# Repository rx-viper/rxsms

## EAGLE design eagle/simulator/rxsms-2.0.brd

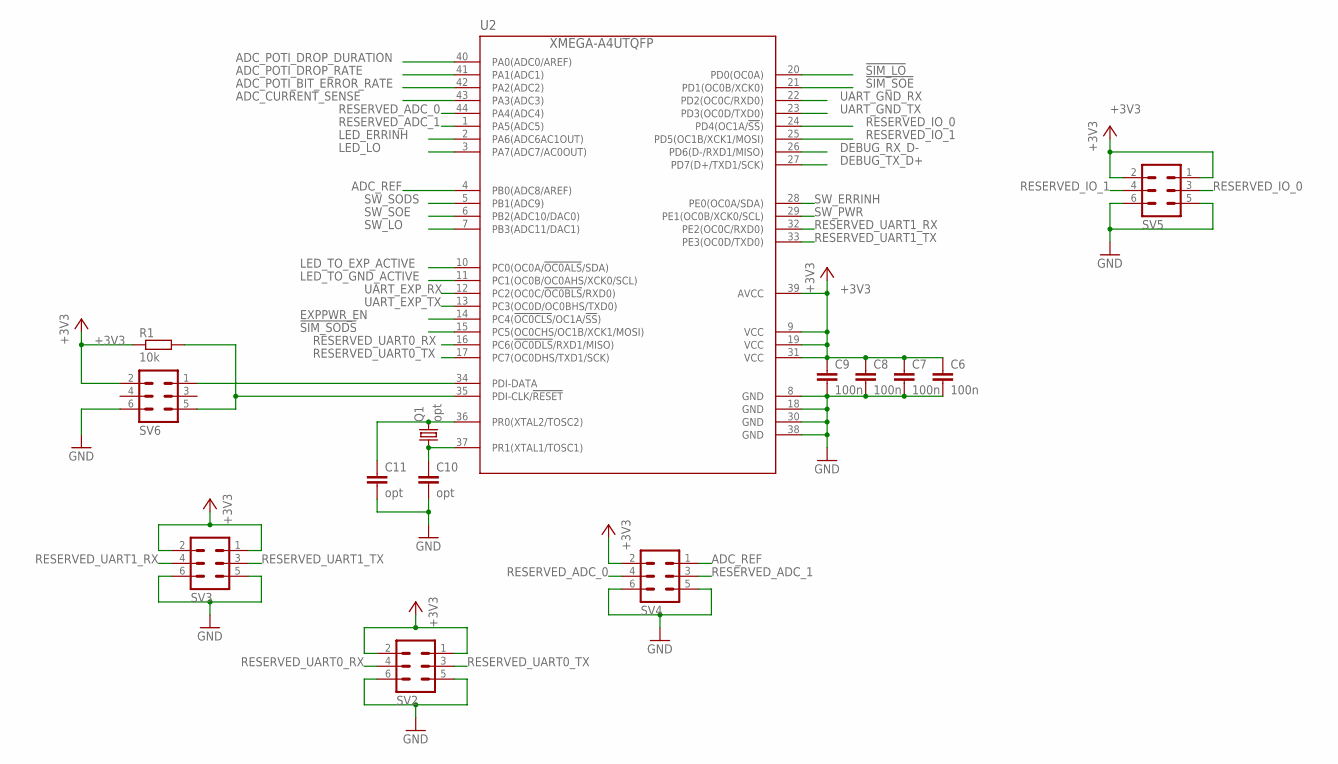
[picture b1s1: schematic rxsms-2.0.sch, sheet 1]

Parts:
C6, C7, C8, C9: 100n; C0805K
C10, C11: opt; C0805K
Q1: opt; HC49/S
R1: 10k; R0805
SV2, SV3, SV4, SV5, SV6: ML6
U2: XMEGA-A4UTQFP; TQFP44

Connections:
!SIM_LO: U2.20 (PD0(OC0A)); also elsewhere on the board
!SIM_SODS: U2.15 (PC5(OC0CHS/OC1B/XCK1/MOSI)); also elsewhere on the board
!SIM_SOE: U2.21 (PD1(OC0B/XCK0)); also elsewhere on the board
+3V3: C6.1, C7.1, C8.1, C9.1, R1.1, SV2.1, SV2.2, SV3.1, SV3.2, SV4.2, SV5.1, SV5.2, SV6.2, U2.9 (VCC), U2.19 (VCC), U2.31 (VCC), U2.39 (AVCC); also elsewhere on the board
ADC_CURRENT_SENSE: U2.43 (PA3(ADC3)); also elsewhere on the board
ADC_POTI_BIT_ERROR_RATE: U2.42 (PA2(ADC2)); also elsewhere on the board
ADC_POTI_DROP_DURATION: U2.40 (PA0(ADC0/AREF)); also elsewhere on the board
ADC_POTI_DROP_RATE: U2.41 (PA1(ADC1)); also elsewhere on the board
ADC_REF: SV4.1, U2.4 (PB0(ADC8/AREF)); also elsewhere on the board
DEBUG_RX_D-: U2.26 (PD6(D-/RXD1/MISO)); also elsewhere on the board
DEBUG_TX_D+: U2.27 (PD7(D+/TXD1/SCK)); also elsewhere on the board
EXPPWR_EN: U2.14 (PC4(!OC0CLS!/OC1A/!SS!)); also elsewhere on the board
GND: C6.2, C7.2, C8.2, C9.2, C10.2, C11.2, SV2.5, SV2.6, SV3.5, SV3.6, SV4.5, SV4.6, SV5.5, SV5.6, SV6.6, U2.8 (GND), U2.18 (GND), U2.30 (GND), U2.38 (GND); also elsewhere on the board
LED_ERRINH: U2.2 (PA6(ADC6AC1OUT)); also elsewhere on the board
LED_LO: U2.3 (PA7(ADC7/AC0OUT)); also elsewhere on the board
LED_TO_EXP_ACTIVE: U2.10 (PC0(OC0A/!OC0ALS!/SDA)); also elsewhere on the board
LED_TO_GND_ACTIVE: U2.11 (PC1(OC0B/OC0AHS/XCK0/SCL)); also elsewhere on the board
unnamed: C10.1, Q1.1, U2.37 (PR1(XTAL1/TOSC1))
unnamed: C11.1, Q1.2, U2.36 (PR0(XTAL2/TOSC2))
unnamed: SV6.1, U2.34 (PDI-DATA)
unnamed: R1.2, SV6.5, U2.35 (PDI-CLK/!RESET)
RESERVED_ADC_0: SV4.4, U2.44 (PA4(ADC4))
RESERVED_ADC_1: SV4.3, U2.1 (PA5(ADC5))
RESERVED_IO_0: SV5.3, U2.24 (PD4(OC1A/!SS!))
RESERVED_IO_1: SV5.4, U2.25 (PD5(OC1B/XCK1/MOSI))
RESERVED_UART0_RX: SV2.4, U2.16 (PC6(!OC0DLS!/RXD1/MISO))
RESERVED_UART0_TX: SV2.3, U2.17 (PC7(OC0DHS/TXD1/SCK))
RESERVED_UART1_RX: SV3.4, U2.32 (PE2(OC0C/RXD0))
RESERVED_UART1_TX: SV3.3, U2.33 (PE3(OC0D/TXD0))
SW_ERRINH: U2.28 (PE0(OC0A/SDA)); also elsewhere on the board
SW_LO: U2.7 (PB3(ADC11/DAC1)); also elsewhere on the board
SW_PWR: U2.29 (PE1(OC0B/XCK0/SCL)); also elsewhere on the board
SW_SODS: U2.5 (PB1(ADC9)); also elsewhere on the board
SW_SOE: U2.6 (PB2(ADC10/DAC0)); also elsewhere on the board
UART_EXP_RX: U2.12 (PC2(OC0C/!OC0BLS!/RXD0)); also elsewhere on the board
UART_EXP_TX: U2.13 (PC3(OC0D/OC0BHS/TXD0)); also elsewhere on the board
UART_GND_RX: U2.22 (PD2(OC0C/RXD0)); also elsewhere on the board
UART_GND_TX: U2.23 (PD3(OC0D/TXD0)); also elsewhere on the board

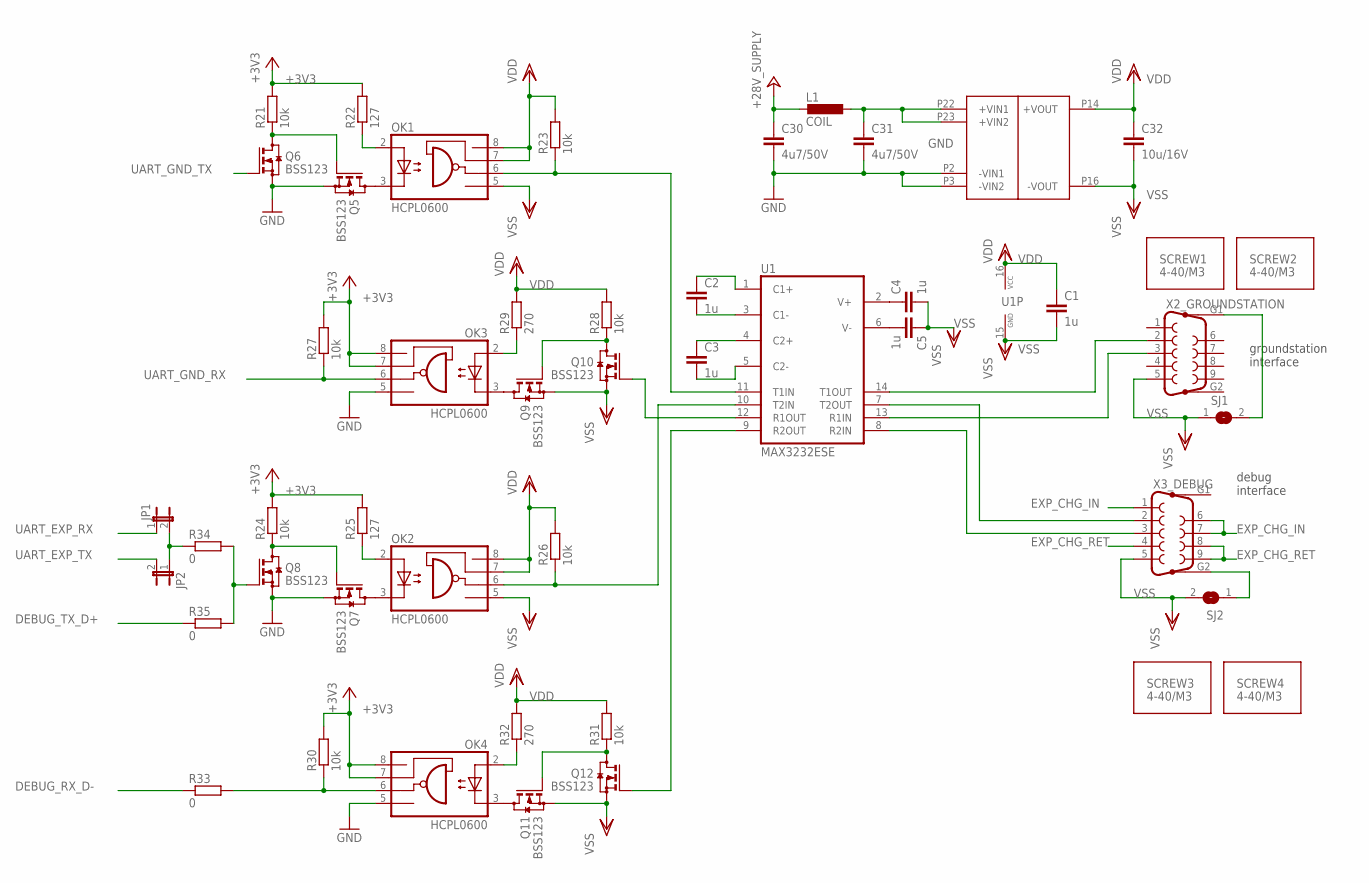
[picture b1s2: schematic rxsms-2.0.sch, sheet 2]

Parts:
C1, C2, C3, C4, C5: 1u; C0805K
C30, C31: 4u7/50V; C0805K
C32: 10u/16V; C0805K
JP1, JP2: JP1E; JP1
L1: COIL; BOURNS-SRR0906
OK1, OK2, OK3, OK4: HCPL0600; SOIC08
Q5, Q6, Q7, Q8, Q9, Q10, Q11, Q12: BSS123; SOT23
R21, R23, R24, R26, R27, R28, R30, R31: 10k; R0805
R22, R25: 127; R0805
R29, R32: 270; R0805
R33, R34, R35: 0; R0805
SCREW1, SCREW2, SCREW3, SCREW4: 4-40/M3; SCREW_DUMMY
SJ1, SJ2: SJ
U1: MAX3232ESE; SO16
U$10: TEN3-2410N
X2_GROUNDSTATION, X3_DEBUG: F09HP

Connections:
+3V3: OK3.7 (VE), OK3.8 (VCC), OK4.7 (VE), OK4.8 (VCC), R21.2, R22.2, R24.2, R25.2, R27.2, R30.2; also elsewhere on the board
+28V_SUPPLY: C30.1, L1.P4 (2); also elsewhere on the board
DEBUG_RX_D-: R33.1; also elsewhere on the board
DEBUG_TX_D+: R35.1; also elsewhere on the board
EXP_CHG_IN: X3_DEBUG.1, X3_DEBUG.6, X3_DEBUG.7; also elsewhere on the board
EXP_CHG_RET: X3_DEBUG.4, X3_DEBUG.8, X3_DEBUG.9; also elsewhere on the board
GND: C30.2, C31.2, OK3.5 (GND), OK4.5 (GND), Q5.2 (S), Q6.2 (S), Q7.2 (S), Q8.2 (S), U$10.P2 (-VIN1), U$10.P3 (-VIN2); also elsewhere on the board
unnamed: C4.1, U1.2 (V+)
unnamed: C5.2, U1.6 (V-)
unnamed: U1.14 (T1OUT), X2_GROUNDSTATION.2
unnamed: C2.2, U1.3 (C1-)
unnamed: C2.1, U1.1 (C1+)
unnamed: C3.1, U1.4 (C2+)
unnamed: C3.2, U1.5 (C2-)
unnamed: U1.13 (R1IN), X2_GROUNDSTATION.3
unnamed: U1.7 (T2OUT), X3_DEBUG.2
unnamed: U1.8 (R2IN), X3_DEBUG.3
unnamed: OK1.3 (C), Q5.3 (D)
unnamed: OK1.6 (VO), R23.1, U1.11 (T1IN)
unnamed: Q5.1 (G), Q6.3 (D), R21.1
unnamed: Q11.1 (G), Q12.3 (D), R31.1
unnamed: OK1.2 (A), R22.1
unnamed: OK2.3 (C), Q7.3 (D)
unnamed: OK2.2 (A), R25.1
unnamed: OK2.6 (VO), R26.1, U1.10 (T2IN)
unnamed: Q7.1 (G), Q8.3 (D), R24.1
unnamed: Q9.1 (G), Q10.3 (D), R28.1
unnamed: OK3.3 (C), Q9.3 (D)
unnamed: OK4.3 (C), Q11.3 (D)
unnamed: OK3.2 (A), R29.1
unnamed: OK4.2 (A), R32.1
unnamed: Q10.1 (G), U1.12 (R1OUT)
unnamed: Q12.1 (G), U1.9 (R2OUT)
unnamed: OK4.6 (VO), R30.1, R33.2
unnamed: Q8.1 (G), R34.2, R35.2
unnamed: SJ1.2, X2_GROUNDSTATION.G1
unnamed: SJ2.1, X3_DEBUG.G2
unnamed: JP1.2, JP2.1, R34.1
unnamed: C31.1, L1.P1 (1), U$10.P22 (+VIN1), U$10.P23 (+VIN2)
UART_EXP_RX: JP1.1; also elsewhere on the board
UART_EXP_TX: JP2.2; also elsewhere on the board
UART_GND_RX: OK3.6 (VO), R27.1; also elsewhere on the board
UART_GND_TX: Q6.1 (G); also elsewhere on the board
VDD: C1.1, C32.1, OK1.7 (VE), OK1.8 (VCC), OK2.7 (VE), OK2.8 (VCC), R23.2, R26.2, R28.2, R29.2, R31.2, R32.2, U1.16 (VCC), U$10.P14 (+VOUT)
VSS: C1.2, C4.2, C5.1, C32.2, OK1.5 (GND), OK2.5 (GND), Q9.2 (S), Q10.2 (S), Q11.2 (S), Q12.2 (S), SJ1.1, SJ2.2, U1.15 (GND), U$10.P16 (-VOUT), X2_GROUNDSTATION.5, X3_DEBUG.5

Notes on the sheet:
groundstation interface
debug interface

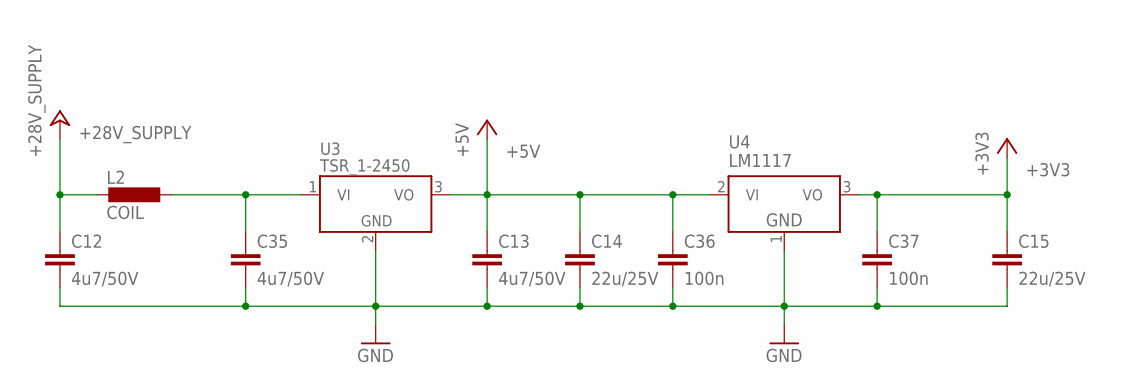
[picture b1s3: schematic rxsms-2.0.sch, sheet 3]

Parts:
C12, C13, C35: 4u7/50V; C0805K
C14, C15: 22u/25V; C0805K
C36, C37: 100n; C0805K
L2: COIL; BOURNS-SRR0906
U3: TSR_1-2450; TSR-1
U4: LM1117; TO252

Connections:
+3V3: C15.1, C37.1, U4.3 (VO); also elsewhere on the board
+5V: C13.1, C14.1, C36.1, U3.3 (VO), U4.2 (VI); also elsewhere on the board
+28V_SUPPLY: C12.1, L2.P4 (2); also elsewhere on the board
GND: C12.2, C13.2, C14.2, C15.2, C35.2, C36.2, C37.2, U3.2 (GND), U4.1 (GND); also elsewhere on the board
VI: C35.1, L2.P1 (1), U3.1 (VI)

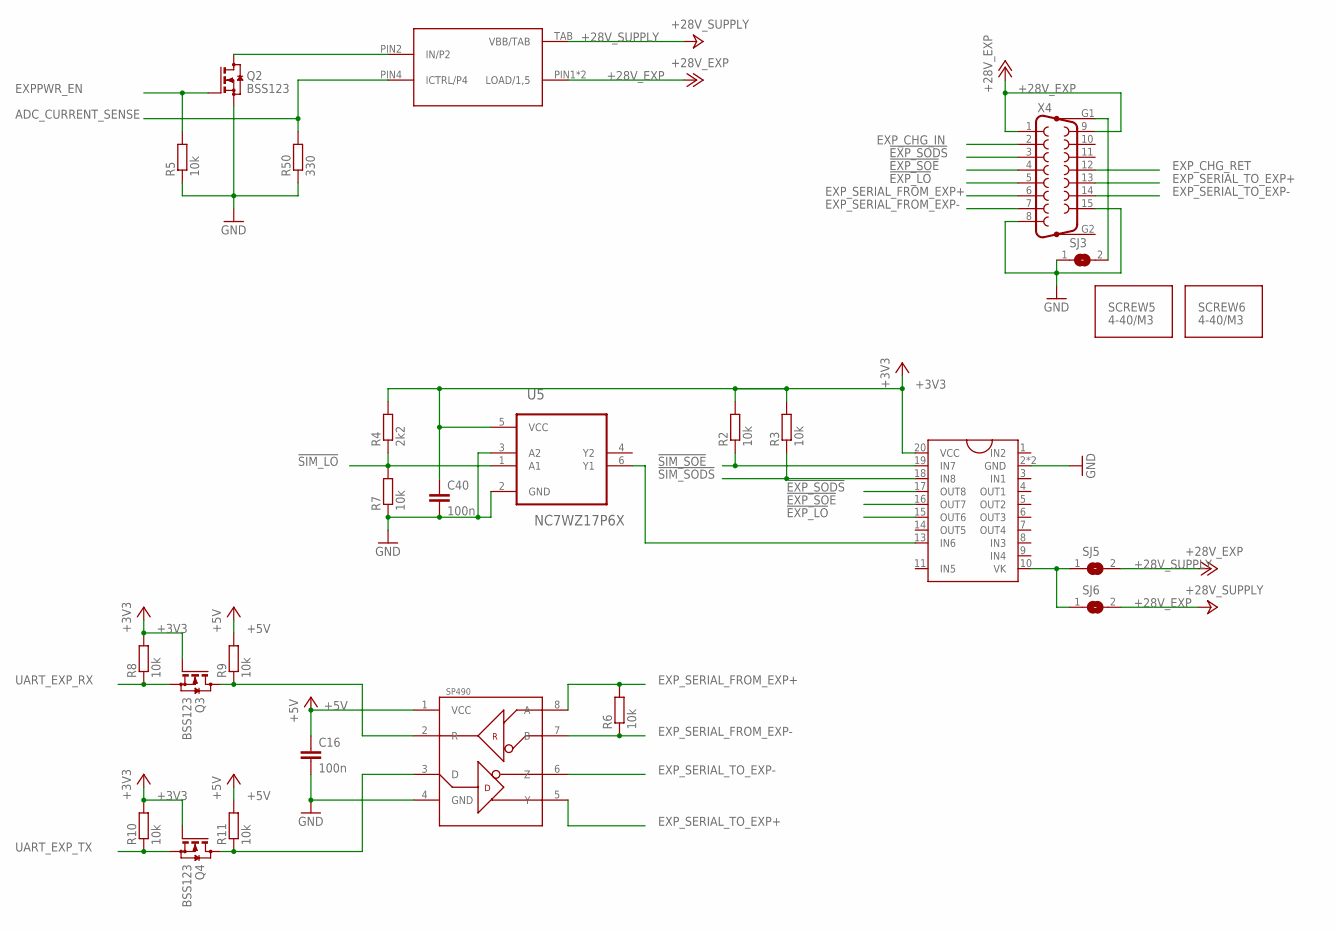
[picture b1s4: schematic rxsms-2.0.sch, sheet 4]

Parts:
C16, C40: 100n; C0805K
Q2, Q3, Q4: BSS123; SOT23
R2, R3, R5, R6, R7, R8, R9, R10, R11: 10k; R0805
R4: 2k2; R0805
R50: 330; R0805
SCREW5, SCREW6: 4-40/M3; SCREW_DUMMY
SJ3, SJ5, SJ6: SJ
U5: NC7WZ17P6X; SOT65P210X110-6N
U$4: UDN2596; DIL20
U$5: SP490; SO08
U$6: BTS6143; TO-252-5-1
X4: F15HP

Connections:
!EXP_LO: U$4.15 (OUT6), X4.5; also elsewhere on the board
!EXP_SODS: U$4.17 (OUT8), X4.3
!EXP_SOE: U$4.16 (OUT7), X4.4
!SIM_LO: R4.1, R7.2, U5.1 (A1); also elsewhere on the board
!SIM_SODS: R3.1, U$4.18 (IN8); also elsewhere on the board
!SIM_SOE: R2.1, U$4.19 (IN7); also elsewhere on the board
+3V3: C40.1, Q3.1 (G), Q4.1 (G), R2.2, R3.2, R4.2, R8.2, R10.2, U5.5 (VCC), U$4.20 (VCC); also elsewhere on the board
+5V: C16.1, R9.2, R11.2, U$5.1 (VCC); also elsewhere on the board
+28V_EXP: SJ6.2, U$6.PIN1 (LOAD/1,5), U$6.PIN5 (LOAD/1,5), X4.1, X4.9
+28V_SUPPLY: SJ5.2, U$6.TAB (VBB/TAB); also elsewhere on the board
ADC_CURRENT_SENSE: R50.2, U$6.PIN4 (ICTRL/P4); also elsewhere on the board
EXPPWR_EN: Q2.1 (G), R5.2; also elsewhere on the board
EXP_CHG_IN: X4.2; also elsewhere on the board
EXP_CHG_RET: X4.12; also elsewhere on the board
EXP_SERIAL_FROM_EXP+: R6.2, U$5.8 (A), X4.6
EXP_SERIAL_FROM_EXP-: R6.1, U$5.7 (B), X4.7
EXP_SERIAL_TO_EXP+: U$5.5 (Y), X4.13
EXP_SERIAL_TO_EXP-: U$5.6 (Z), X4.14
GND: C16.2, C40.2, Q2.2 (S), R5.1, R7.1, R50.1, SJ3.1, U5.2 (GND), U5.3 (A2), U$4.2 (GND), U$4.12 (GND), U$5.4 (GND), X4.8, X4.15; also elsewhere on the board
unnamed: Q2.3 (D), U$6.PIN2 (IN/P2)
unnamed: Q3.3 (D), R9.1, U$5.2 (R)
unnamed: Q4.3 (D), R11.1, U$5.3 (D)
unnamed: SJ5.1, SJ6.1, U$4.10 (VK)
unnamed: SJ3.2, X4.G1
unnamed: U5.6 (Y1), U$4.13 (IN6)
UART_EXP_RX: Q3.2 (S), R8.1; also elsewhere on the board
UART_EXP_TX: Q4.2 (S), R10.1; also elsewhere on the board

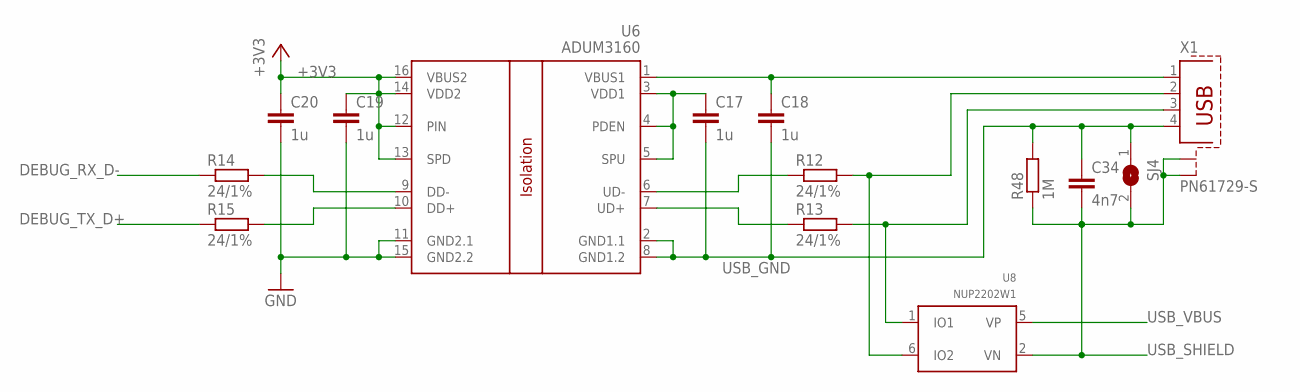
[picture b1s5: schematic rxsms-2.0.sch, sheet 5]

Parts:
C17, C18, C19, C20: 1u; C0805K
C34: 4n7; C0805K
R12, R13, R14, R15: 24/1%; R0805
R48: 1M; R0805
SJ4: SJ
U6: ADUM3160; SO-16W
U8: NUP2202W1; SOT363_PHILIPS
X1: PN61729-S

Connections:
+3V3: C19.1, C20.1, U6.12 (PIN), U6.13 (SPD), U6.14 (VDD2), U6.16 (VBUS2); also elsewhere on the board
DEBUG_RX_D-: R14.1; also elsewhere on the board
DEBUG_TX_D+: R15.1; also elsewhere on the board
GND: C19.2, C20.2, U6.11 (GND2.1), U6.15 (GND2.2); also elsewhere on the board
unnamed: C17.1, U6.3 (VDD1), U6.4 (PDEN), U6.5 (SPU)
unnamed: R12.1, U6.6 (UD-)
unnamed: R13.1, U6.7 (UD+)
unnamed: R12.2, U8.6 (IO2), X1.2
unnamed: R14.2, U6.9 (DD-)
unnamed: R15.2, U6.10 (DD+)
unnamed: R13.2, U8.1 (IO1), X1.3
USB_GND: C17.2, C18.2, C34.1, R48.2, SJ4.1, U6.2 (GND1.1), U6.8 (GND1.2), X1.4
USB_SHIELD: C34.2, R48.1, SJ4.2, U8.2 (VN), X1.S1, X1.S2
USB_VBUS: C18.1, U6.1 (VBUS1), U8.5 (VP), X1.1

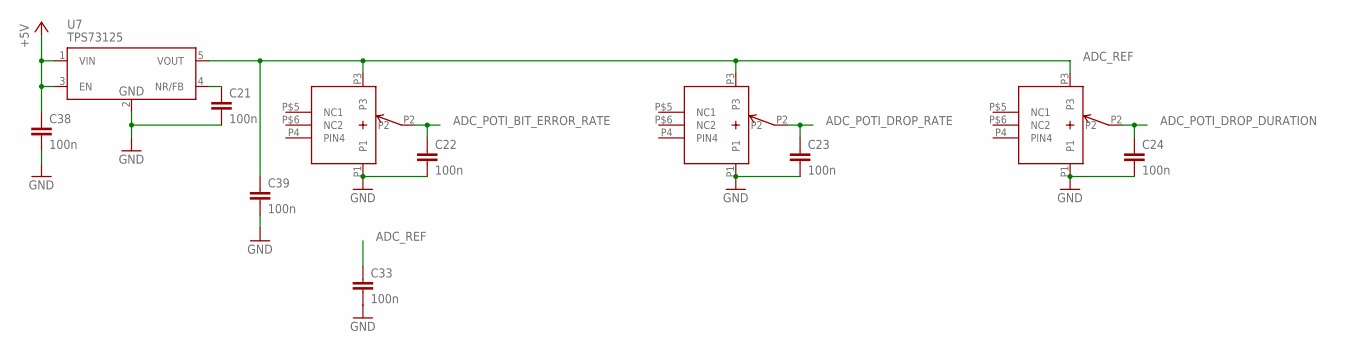
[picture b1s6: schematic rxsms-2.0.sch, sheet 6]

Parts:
C21, C22, C23, C24, C33, C38, C39: 100n; C0805K
U7: TPS73125; SOT25
U$7_BER, U$8_DROPR, U$9_DROPDUR: 50k; VERT_POTI

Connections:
+5V: C38.1, U7.1 (VIN), U7.3 (EN); also elsewhere on the board
ADC_POTI_BIT_ERROR_RATE: C22.1, U$7_BER.P2; also elsewhere on the board
ADC_POTI_DROP_DURATION: C24.1, U$9_DROPDUR.P2; also elsewhere on the board
ADC_POTI_DROP_RATE: C23.1, U$8_DROPR.P2; also elsewhere on the board
ADC_REF: C33.1, C39.1, U7.5 (VOUT), U$7_BER.P3, U$8_DROPR.P3, U$9_DROPDUR.P3; also elsewhere on the board
GND: C21.2, C22.2, C23.2, C24.2, C33.2, C38.2, C39.2, U7.2 (GND), U$7_BER.P1, U$8_DROPR.P1, U$9_DROPDUR.P1; also elsewhere on the board
unnamed: C21.1, U7.4 (NR/FB)

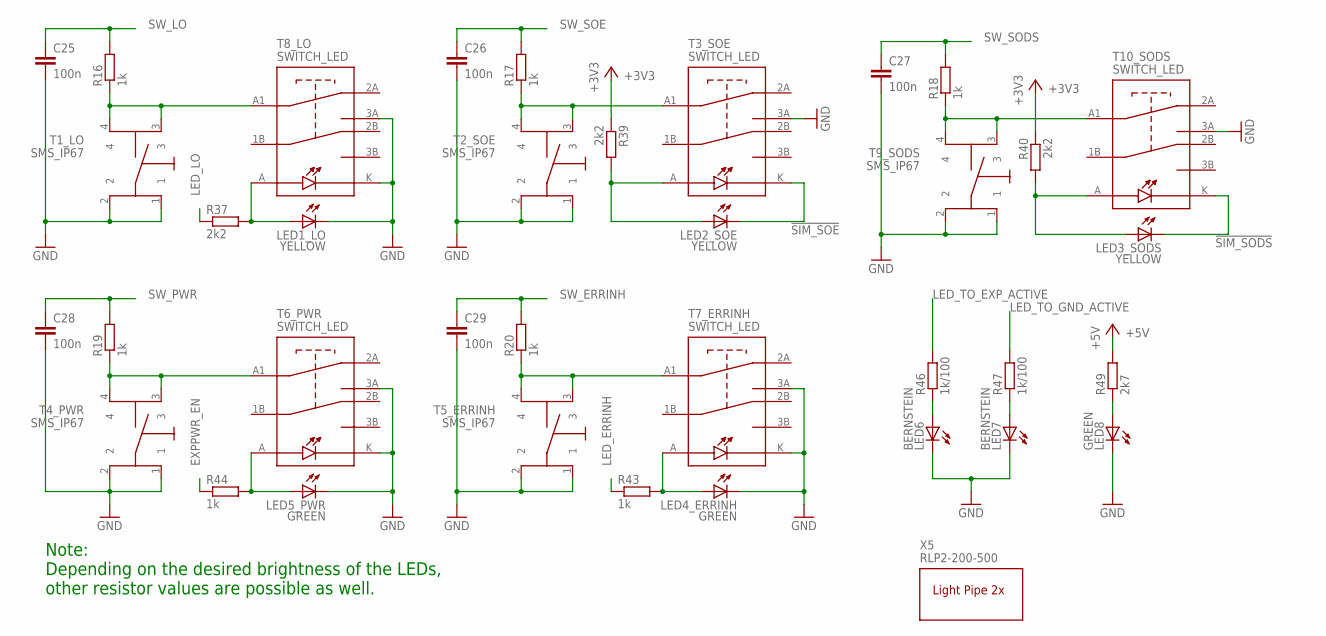
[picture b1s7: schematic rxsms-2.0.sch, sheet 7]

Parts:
C25, C26, C27, C28, C29: 100n; C0805K
LED1_LO, LED2_SOE, LED3_SODS: YELLOW; CHIPLED_1206
LED4_ERRINH, LED5_PWR, LED8: GREEN; CHIPLED_1206
LED6, LED7: BERNSTEIN; CHIPLED_1206
R16, R17, R18, R19, R20, R43, R44: 1k; R0805
R37, R39, R40: 2k2; R0805
R46, R47: 1k/100; R0805
R49: 2k7; R0805
T1_LO, T2_SOE, T4_PWR, T5_ERRINH, T9_SODS: SMS_IP67; IP67
T3_SOE, T6_PWR, T7_ERRINH, T8_LO, T10_SODS: SWITCH_LED
X5: RLP2-200-500

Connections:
!SIM_SODS: LED3_SODS.C, T10_SODS.K; also elsewhere on the board
!SIM_SOE: LED2_SOE.C, T3_SOE.K; also elsewhere on the board
+3V3: R39.1, R40.1; also elsewhere on the board
+5V: R49.2; also elsewhere on the board
EXPPWR_EN: R44.1; also elsewhere on the board
GND: C25.2, C26.2, C27.2, C28.2, C29.2, LED1_LO.C, LED4_ERRINH.C, LED5_PWR.C, LED6.C, LED7.C, LED8.C, T1_LO.1, T1_LO.2, T2_SOE.1, T2_SOE.2, T3_SOE.3A, T4_PWR.1, T4_PWR.2, T5_ERRINH.1, T5_ERRINH.2, T6_PWR.3A, T6_PWR.K, T7_ERRINH.3A, T7_ERRINH.K, T8_LO.3A, T8_LO.K, T9_SODS.1, T9_SODS.2, T10_SODS.3A; also elsewhere on the board
LED_ERRINH: R43.1; also elsewhere on the board
LED_LO: R37.1; also elsewhere on the board
LED_TO_EXP_ACTIVE: R46.2; also elsewhere on the board
LED_TO_GND_ACTIVE: R47.2; also elsewhere on the board
unnamed: LED2_SOE.A, R39.2, T3_SOE.A
unnamed: LED3_SODS.A, R40.2, T10_SODS.A
unnamed: LED8.A, R49.1
unnamed: R16.1, T1_LO.3, T1_LO.4, T8_LO.A1 (1A)
unnamed: R17.1, T2_SOE.3, T2_SOE.4, T3_SOE.A1 (1A)
unnamed: R18.1, T9_SODS.3, T9_SODS.4, T10_SODS.A1 (1A)
unnamed: LED1_LO.A, R37.2, T8_LO.A
unnamed: R19.1, T4_PWR.3, T4_PWR.4, T6_PWR.A1 (1A)
unnamed: R20.1, T5_ERRINH.3, T5_ERRINH.4, T7_ERRINH.A1 (1A)
unnamed: LED4_ERRINH.A, R43.2, T7_ERRINH.A
unnamed: LED5_PWR.A, R44.2, T6_PWR.A
unnamed: LED6.A, R46.1
unnamed: LED7.A, R47.1
SW_ERRINH: C29.1, R20.2; also elsewhere on the board
SW_LO: C25.1, R16.2; also elsewhere on the board
SW_PWR: C28.1, R19.2; also elsewhere on the board
SW_SODS: C27.1, R18.2; also elsewhere on the board
SW_SOE: C26.1, R17.2; also elsewhere on the board

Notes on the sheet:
Note: Depending on the desired brightness of the LEDs, other resistor values are possible as well.

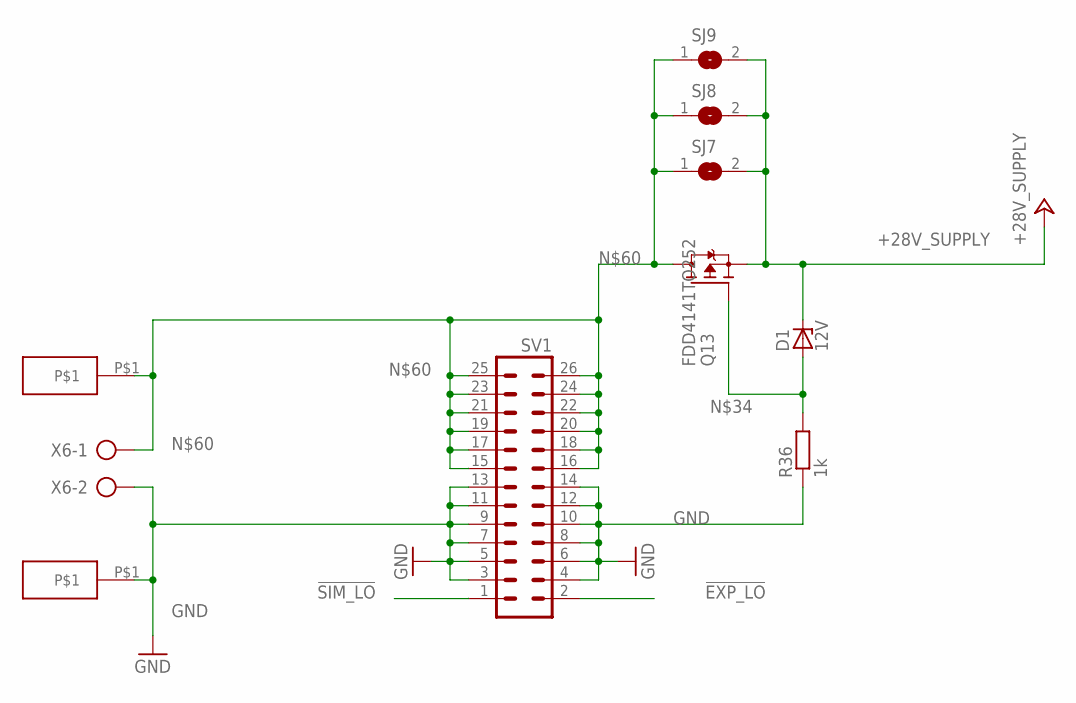
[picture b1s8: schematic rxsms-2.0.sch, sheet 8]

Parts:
D1: 12V; DO34Z7
Q13: FDD4141TO252; TO252
R36: 1k; R0805
SJ7, SJ8, SJ9: SJ
SV1: ML26L
U$3: black; JACK
U$9: red; JACK
X6: AK500/2

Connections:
!EXP_LO: SV1.2; also elsewhere on the board
!SIM_LO: SV1.1; also elsewhere on the board
+28V_SUPPLY: D1.C, Q13.2 (S), SJ7.2, SJ8.2, SJ9.2; also elsewhere on the board
GND: R36.1, SV1.3, SV1.4, SV1.5, SV1.6, SV1.7, SV1.8, SV1.9, SV1.10, SV1.11, SV1.12, SV1.13, SV1.14, U$3.P$1, X6.2; also elsewhere on the board
unnamed: D1.A, Q13.1 (G), R36.2
unnamed: Q13.3 (D), SJ7.1, SJ8.1, SJ9.1, SV1.15, SV1.16, SV1.17, SV1.18, SV1.19, SV1.20, SV1.21, SV1.22, SV1.23, SV1.24, SV1.25, SV1.26, U$9.P$1, X6.1

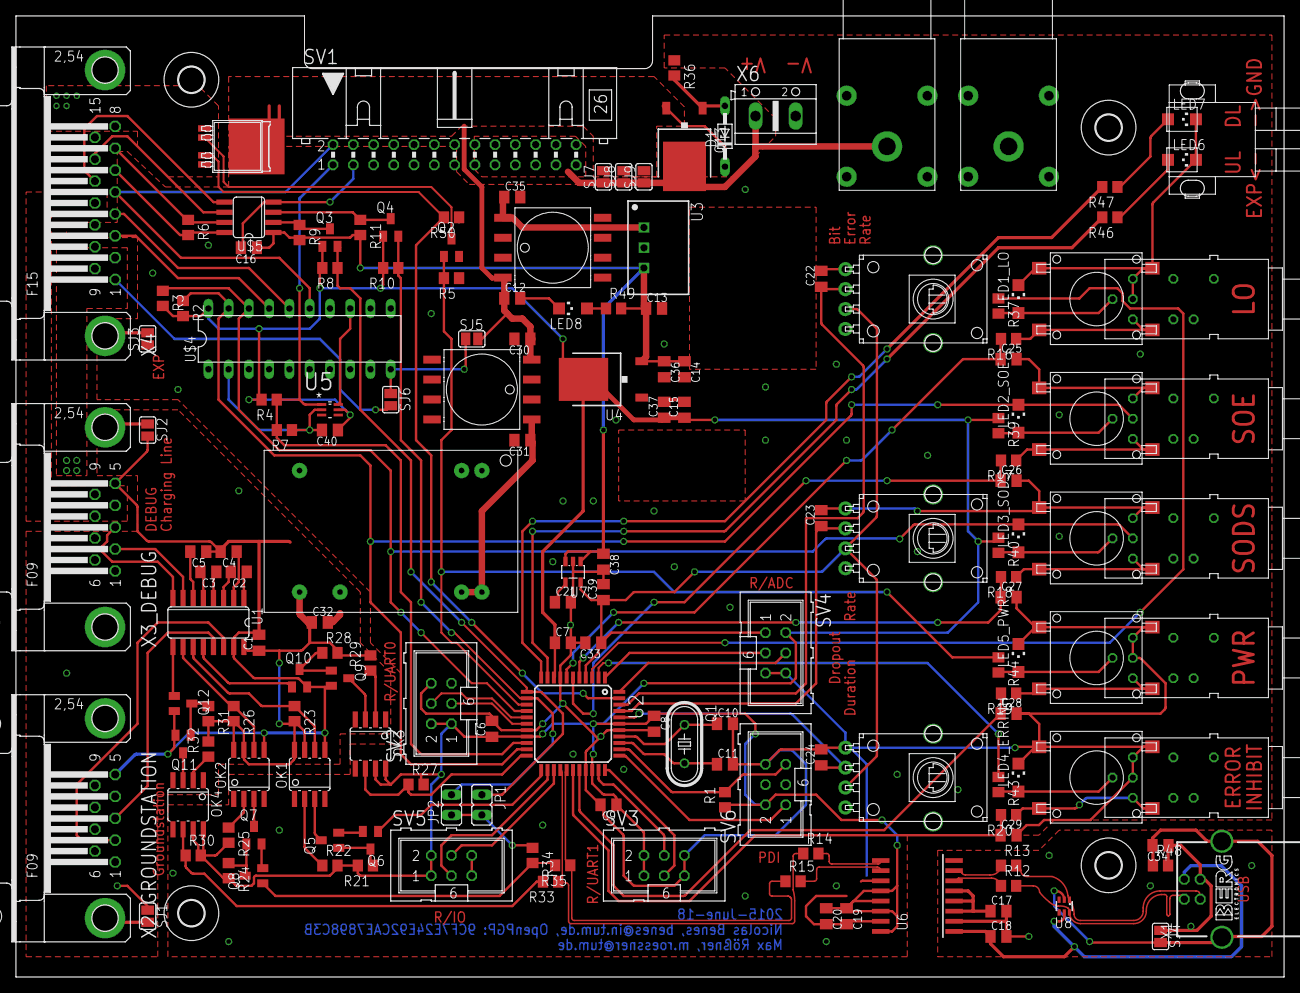
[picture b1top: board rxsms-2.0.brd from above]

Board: 2 copper layers, 159.0 x 120.5 mm, 174 parts (0 on the bottom side), 117 nets.

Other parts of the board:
U$1, U$2, U$7, U$8: 3,2

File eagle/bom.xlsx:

Qty | Value | Device | Package | Parts | Description | OC_BUERKLIN | OC_FARNELL | OC_RS
1 |  | AK500/2 | AK500/2 | X6 | CONNECTOR |  | 1131855
2 |  | F09HP | F09HP | X2_GROUNDSTATION, X3_DEBUG | SUB-D |  | 1207597 (+2x 1855027)
1 |  | F15HP | F15HP | X4 | SUB-D |  | 1207598 (+2x 1855027)
2 |  | JP1E | JP1 | JP1, JP2 | JUMPER
1 |  | ML26L | ML26L | SV1 | HARTING |  | 1096983
5 |  | ML6 | ML6 | SV2, SV3, SV4, SV5, SV6 | HARTING |  | 1096984 | 740-7105
4 |  | SJ | SJ | SJ1, SJ2, SJ3, SJ4 | SMD solder JUMPER
1 | 100k | R-EU_R0805 | R0805 | R7 | RESISTOR, European symbol |  | 2333538
20 | 100n | C-EUC0805K | C0805K | C6, C7, C8, C9, C16, C21, C22, C23, C24, C25, C26, C27, C28, C29, C33, C36, C37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 | CAPACITOR, European symbol |  | 1759265
17 | 10k | R-EU_R0805 | R0805 | R1, R2, R3, R5, R6, R8, R9, R10, R11, R21, R23, R24, R26, R27, R28, R30, R31 | RESISTOR, European symbol |  | 1887308
1 | 10u/16V | C-EUC0805K | C0805K | C32 | CAPACITOR, European symbol |  | 2320856
2 | 127 | R-EU_R0805 | R0805 | R22, R25 | RESISTOR, European symbol |  | 2141745
1 | 150 | R-EU_R0805 | R0805 | R49 | RESISTOR, European symbol |  | 1099794
1 | 1M | R-EU_R0805 | R0805 | R48 | RESISTOR, European symbol |  | 2332111
5 | 1k | R-EU_R0805 | R0805 | R16, R17, R18, R19, R20 | RESISTOR, European symbol |  | 9237496
9 | 1u | C-EUC0805K | C0805K | C1, C2, C3, C4, C5, C17, C18, C19, C20 | CAPACITOR, European symbol |  | 2320853
1 | 22k | R-EU_R0805 | R0805 | R4 | RESISTOR, European symbol |  | 2303686
2 | 22u/16V | C-EUC0805K | C0805K | C14, C15 | CAPACITOR, European symbol |  | 2346925
4 | 24/1% | R-EU_R0805 | R0805 | R12, R13, R14, R15 | RESISTOR, European symbol |  | 1894163
2 | 270 | R-EU_R0805 | R0805 | R29, R32 | RESISTOR, European symbol |  | 2008375 | 740-9019
1 | 330 | R-EU_R0805 | R0805 | R50 | RESISTOR, European symbol |  | 1500705
1 | 3V | ZENER-DIODESOT23 | SOT23 | D1 | Z-Diode |  | 1081418
1 | 4n7 | C-EUC0805K | C0805K | C34 | CAPACITOR, European symbol |  | 1759241
5 | 4u7/50V | C-EUC0805K | C0805K | C12, C13, C30, C31, C35 | CAPACITOR, European symbol |  | 2210979
3 | 50k | STRK11K | VERT_POTI | U$7_BER, U$8_DROPR, U$9_DROPDUR | Potentiometer |  | 1345093
12 | 68 | R-EU_R0805 | R0805 | R36, R37, R38, R39, R40, R41, R42, R43, R44, R45, R46, R47 | RESISTOR, European symbol |  | 2074509
1 | ADUM3160 | ADUM3160 | SO-16W | U6 |  |  | 1843660
2 | BERNSTEIN | LEDCHIPLED_1206 | CHIPLED_1206 | LED6, LED7 | LED |  | 2322083
11 | BSS123 | BSS123 | SOT23 | Q2, Q3, Q4, Q5, Q6, Q7, Q8, Q9, Q10, Q11, Q12 | N-CHANNEL MOS FET |  | 9558640RL | 545-0135
1 | BTS6143 | BTS6143 | TO-252-5-1 | U$6 |  |  | 1440813
2 | COIL | COIL | BOURNS-SRR0906 | U$11, U$12 |  |  | 2333799
3 | GREEN | LEDCHIPLED_1206 | CHIPLED_1206 | LED4_ERRINH, LED5_PWR, LED8 | LED |  | 2099244
4 | HCPL0600 | HCPL0600 | SOIC08 | OK1, OK2, OK3, OK4 | HEWLETT PACKARD OPTO COUPLER |  | 9994696
1 | LM1117 | LM1117 | TO252 | U4 |  |  | 1685603
1 | MAX3232ESE | MAX3232ESE | SO16 | U1 | True RS-232 Transceivers 3.0V to 5.5V, Low-Power |  | 9725539
1 | NC7WZ17P6X | NC7WZ17P6X | SOT65P210X110-6N | U5 | Dual Buffer |  | 1651986
1 | NUP2202W1 | NUP2202W1 | SOT363_PHILIPS | U8 |  |  |  | 463-690
1 | PN61729-S | PN61729-S | PN61729-S | X1 | BERG USB connector |  | 1642035 | 515-1989
1 | RLP2-200-500 | RLP2-200-500 | RLP2-200-500 | X5 |  |  | 1886474
5 | SMS_IP67 | SMS_IP67 | IP67 | T1_LO, T2_SOE, T4_PWR, T5_ERRINH, T9_SODS | Groﾟer Tastschalter Taster Switch Schalter |  | 1217758
1 | SP490 | SP490 | SO08 | U$5 |  |  | 9387234
3 | SWITCH_LED | SWITCH_LED | SWITCH_LED | T3_SOE, T8_LO, T10_SODS |  | 12 G 203
2 | SWITCH_LED | SWITCH_LED | SWITCH_LED | T6_PWR, T7_ERRINH |  | 12 G 205
1 | TEN3-2410N | TEN3-2410N | TEN3-2410N | U$10 |  |  |  | 801-9330
1 | TPS73125 | TPS731 | SOT25 | U7 |  |  | 2112625
1 | TSR_1-2450 | TSR_1-2450 | TSR-1 | U3 | TRACO TSR-1 Series |  | 1696320
1 | UDN2596 | UDN2596 | DIL20 | U$4 |  |  | 1103848
1 | XMEGA-A4UTQFP | XMEGA-A4UTQFP | TQFP44 | U2 | Atmel XMega A4U series processor |  | 2066309
3 | YELLOW | LEDCHIPLED_1206 | CHIPLED_1206 | LED1_LO, LED2_SOE, LED3_SODS | LED |  | 2099249
2 | opt | C-EUC0805K | C0805K | C10, C11 | CAPACITOR, European symbol
1 | opt | CRYSTALHC49S | HC49/S | Q1 | CRYSTAL |  | 1667008
3 | 0 | R-EU_R0805 | R0805 | R33, R34, R35 | RESISTOR, European symbol |  | 2309112

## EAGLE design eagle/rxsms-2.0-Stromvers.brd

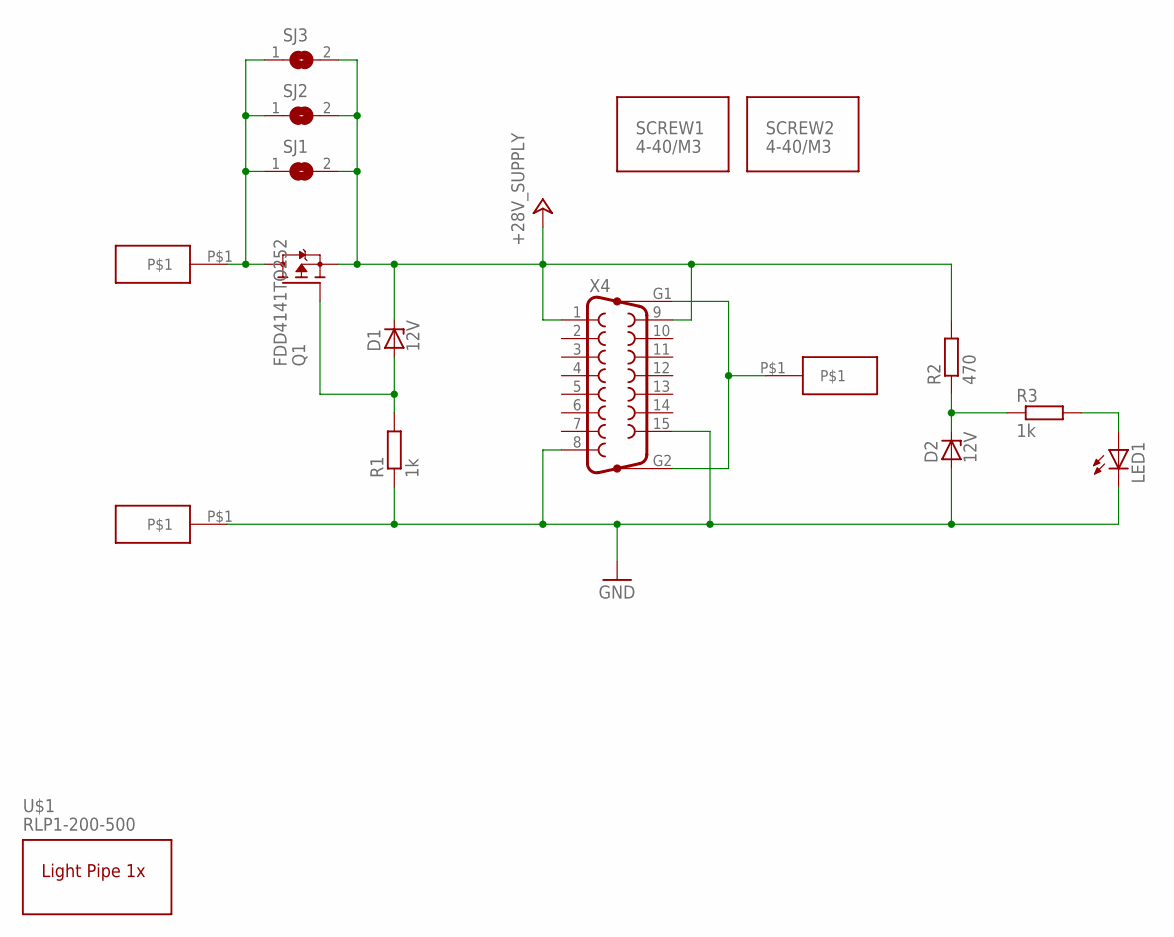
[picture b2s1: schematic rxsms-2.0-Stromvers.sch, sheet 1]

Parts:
D1, D2: 12V; DO34Z7
LED1: LEDCHIPLED_0805; CHIPLED_0805
Q1: FDD4141TO252; TO252
R1, R3: 1k; R0805
R2: 470; R0805
SJ1, SJ2, SJ3: SJ
U$1: RLP1-200-500
U$3, U$4, U$5: JACK
X4: F15HP

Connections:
+28V_SUPPLY: D1.C, Q1.2 (S), R2.2, SJ1.2, SJ2.2, SJ3.2, X4.1, X4.9; also elsewhere on the board
BLUB: Q1.3 (D), SJ1.1, SJ2.1, SJ3.1, U$3.P$1
GND: D2.A, LED1.C, R1.1, U$4.P$1, X4.8, X4.15; also elsewhere on the board
unnamed: D2.C, R2.1, R3.1
unnamed: D1.A, Q1.1 (G), R1.2
unnamed: LED1.A, R3.2
PE: U$5.P$1, X4.G1, X4.G2

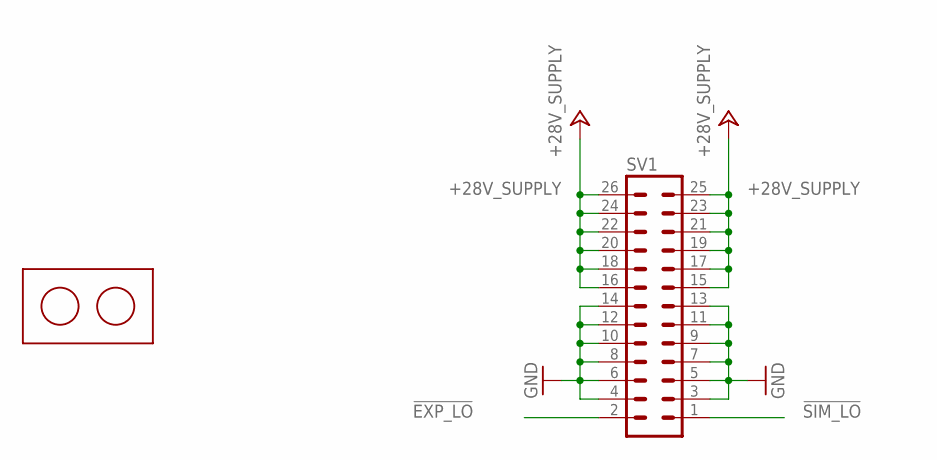
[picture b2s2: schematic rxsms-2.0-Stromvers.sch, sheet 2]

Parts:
SV1: ML26L
U$6: BUERKLIN17H912

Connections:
+28V_SUPPLY: SV1.15, SV1.16, SV1.17, SV1.18, SV1.19, SV1.20, SV1.21, SV1.22, SV1.23, SV1.24, SV1.25, SV1.26; also elsewhere on the board
GND: SV1.3, SV1.4, SV1.5, SV1.6, SV1.7, SV1.8, SV1.9, SV1.10, SV1.11, SV1.12, SV1.13, SV1.14; also elsewhere on the board

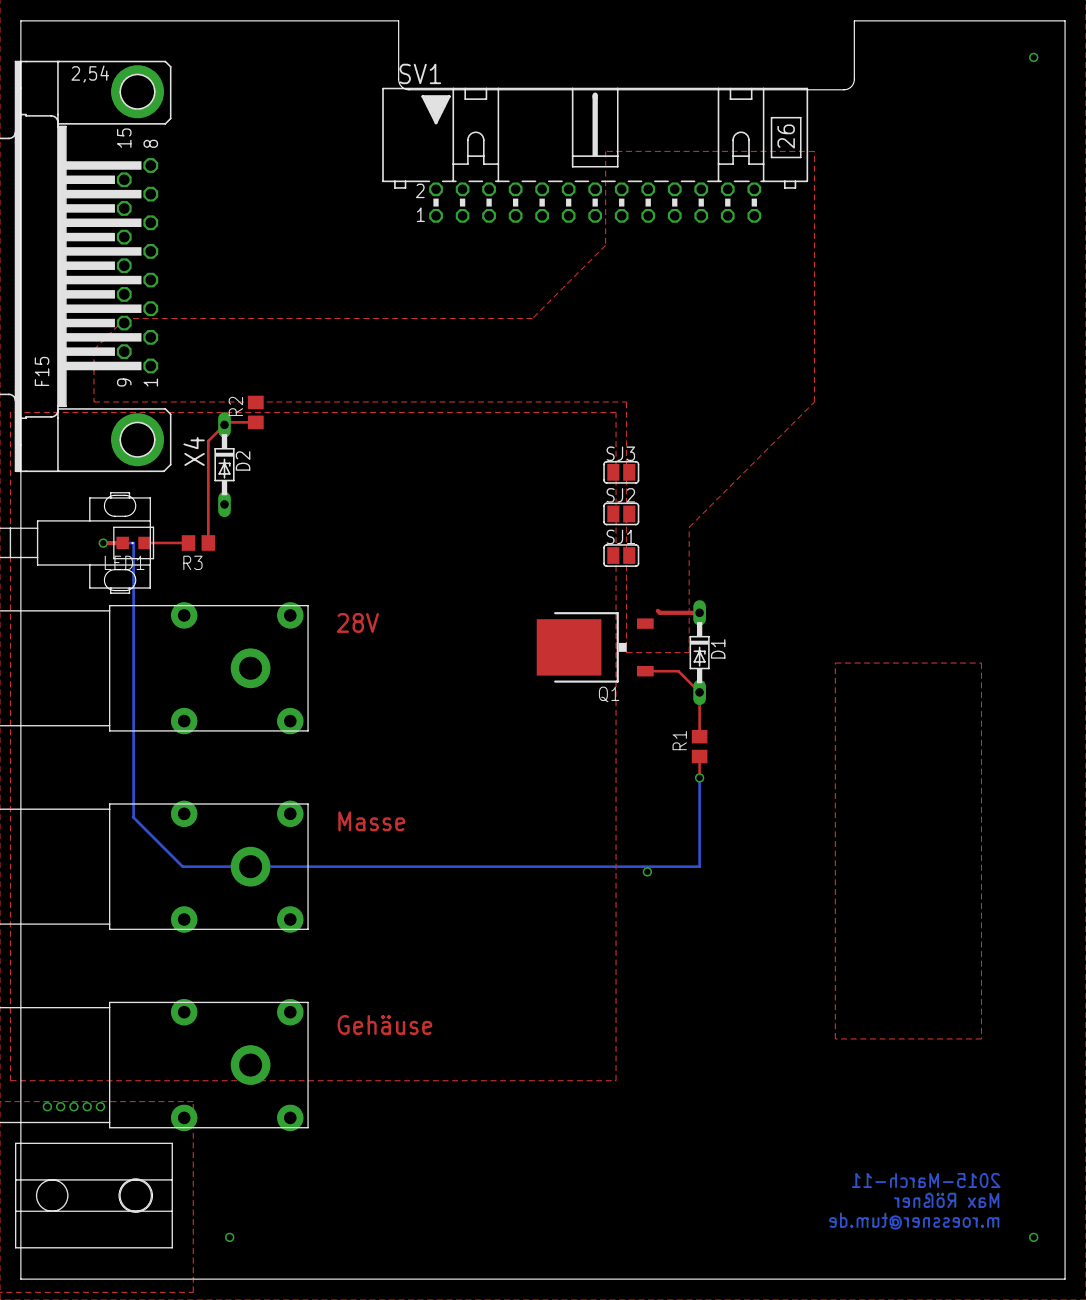
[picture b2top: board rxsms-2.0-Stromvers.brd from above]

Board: 2 copper layers, 100.0 x 120.5 mm, 17 parts (0 on the bottom side), 7 nets.

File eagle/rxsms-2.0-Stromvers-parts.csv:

"Part";"Value";"Device";"Package";"Description";"MF";"MPN";"OC_BUERKLIN";"OC_FARNELL";"OC_NEWARK";"OC_RS";
"D1";"12V";"ZENER-DIODEDO34-7";"DO34Z7";"Z-Diode";"";"";"";"1779204";"";"";
"D2";"12V";"ZENER-DIODEDO34-7";"DO34Z7";"Z-Diode";"";"";"";"1779204";"";"";
"LED1";"";"LEDCHIPLED_0805";"CHIPLED_0805";"LED";"";"";"";"";"";"692-0957";
"Q1";"FDD4141TO252";"FDD4141TO252";"TO252";"P-Channel PowerTrench® MOSFET";"";"";"";"2101406";"";"";
"R1";"1k";"R-EU_R0805";"R0805";"RESISTOR, European symbol";"";"";"";"";"";"";
"R2";"470";"R-EU_R0805";"R0805";"RESISTOR, European symbol";"";"";"";"";"";"";
"R3";"1k";"R-EU_R0805";"R0805";"RESISTOR, European symbol";"";"";"";"";"";"";
"SJ1";"";"SJ";"SJ";"SMD solder JUMPER";"";"";"";"";"";"";
"SJ2";"";"SJ";"SJ";"SMD solder JUMPER";"";"";"";"";"";"";
"SJ3";"";"SJ";"SJ";"SMD solder JUMPER";"";"";"";"";"";"";
"SV1";"";"ML26L";"ML26L";"HARTING";"";"";"";"1096983 (Gegenstück: 1200506 oder 1097038)";"unknown";"";
"U$1";"RLP1-200-500";"RLP1-200-500";"RLP1-200-500";"";"";"";"";"1887972";"";"752-9141";
"U$3";"JACK";"JACK";"JACK";"";"";"";"";"1854507 (black), 1854508 (red), 1854511 (blue), 1854510 (yellow)";"";"";
"U$4";"JACK";"JACK";"JACK";"";"";"";"";"1854507 (black), 1854508 (red), 1854511 (blue), 1854510 (yellow)";"";"";
"U$5";"JACK";"JACK";"JACK";"";"";"";"";"1854507 (black), 1854508 (red), 1854511 (blue), 1854510 (yellow)";"";"";
"U$6";"BUERKLIN17H912";"BUERKLIN17H912";"BUERKLIN17H912";"";"";"";"17H912";"";"";"";
"X4";"";"F15HP";"F15HP";"SUB-D";"";"";"";"1207598 + 2x 1855027";"unknown";"";
